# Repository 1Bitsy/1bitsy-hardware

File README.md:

# 1BitSy

This project includes 1BitSy evaluation boards. These boards are breadboard friendly STM32 (eventually other MCUs will be considered) with exposed Cortex JTAG and SWD interfaces. This allows the use of the Black Magic Probe, instead of the usually very limited built in debugger hardware.

Currently we have the following eval boards:

* 1BitSy V1.0d -> STM32F4x5RGT6

You can find the datasheet of the STM32F415RGT6 chip on the
[STMicroelectronics website](http://www.st.com/content/st_com/en/products/microcontrollers/stm32-32-bit-arm-cortex-mcus/stm32f4-series/stm32f405-415/stm32f415rg.html).

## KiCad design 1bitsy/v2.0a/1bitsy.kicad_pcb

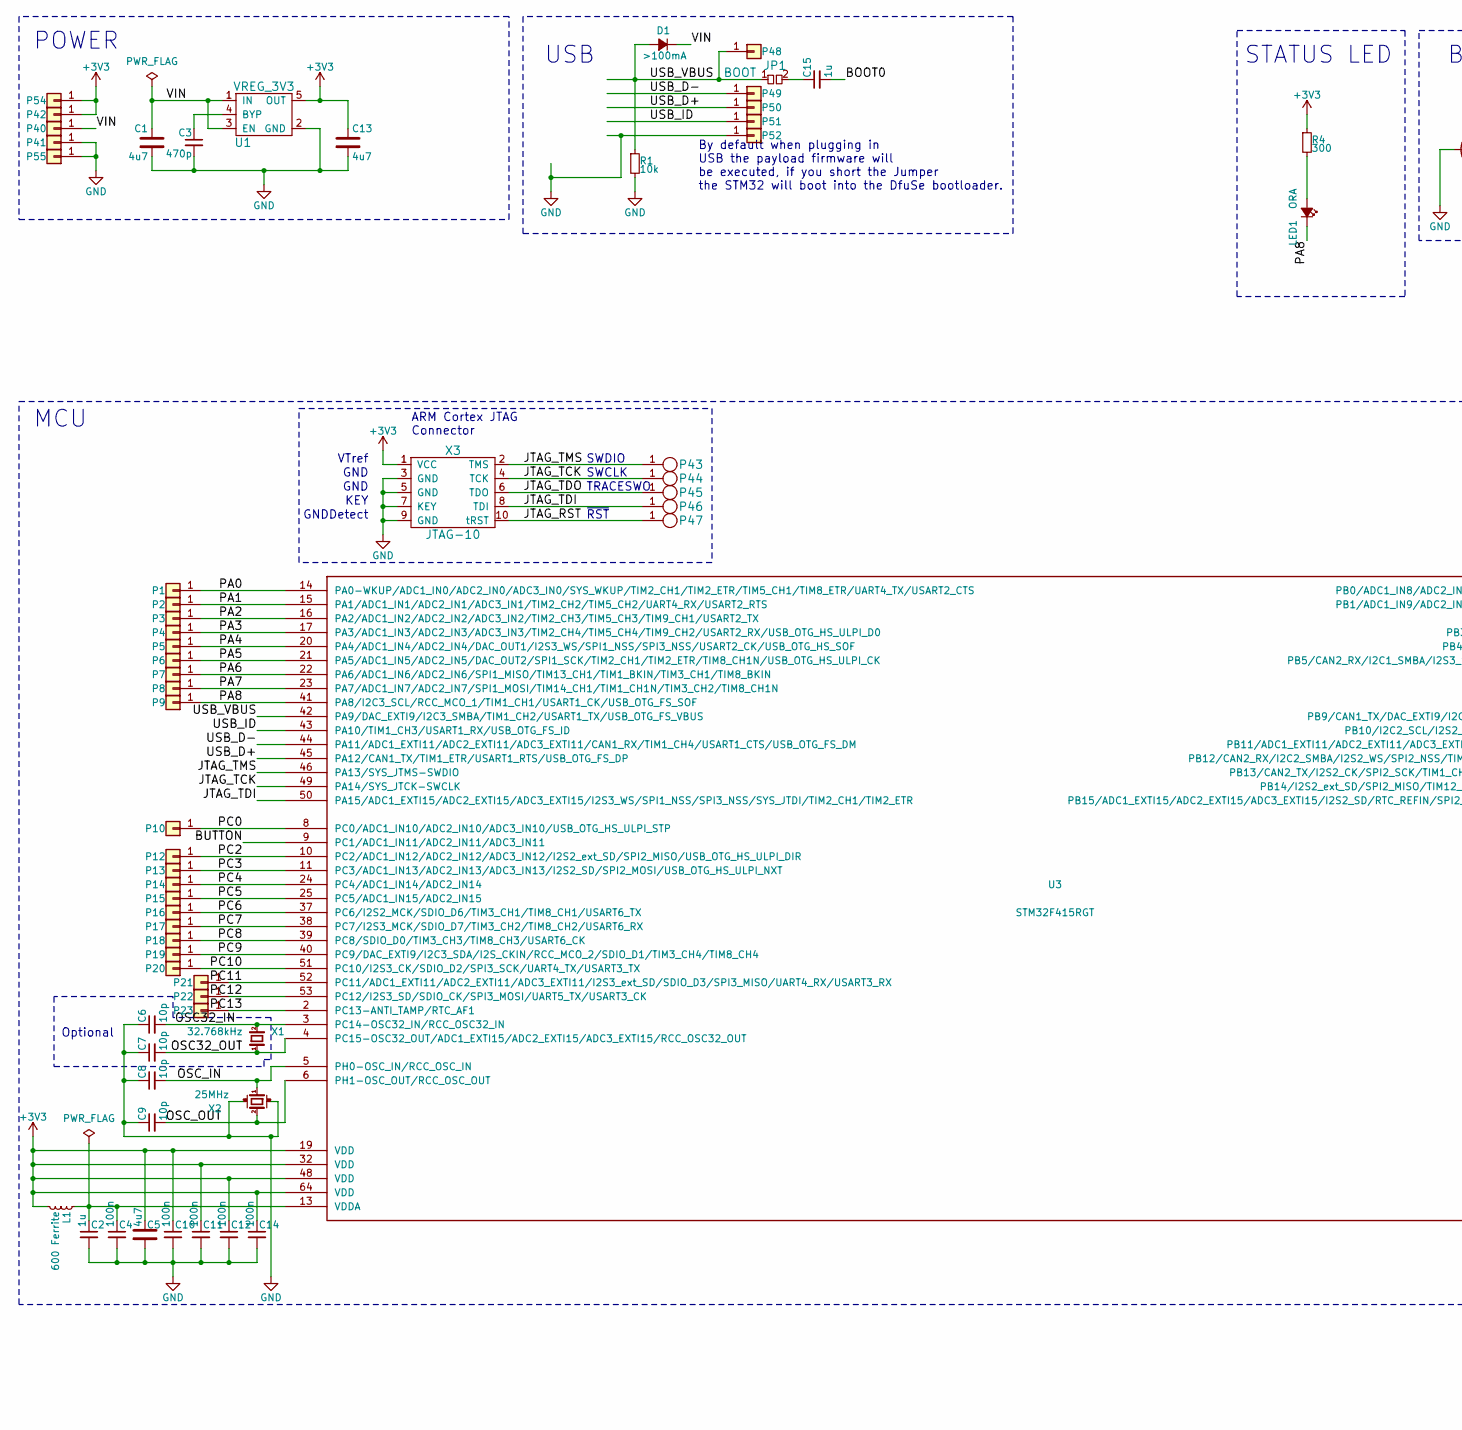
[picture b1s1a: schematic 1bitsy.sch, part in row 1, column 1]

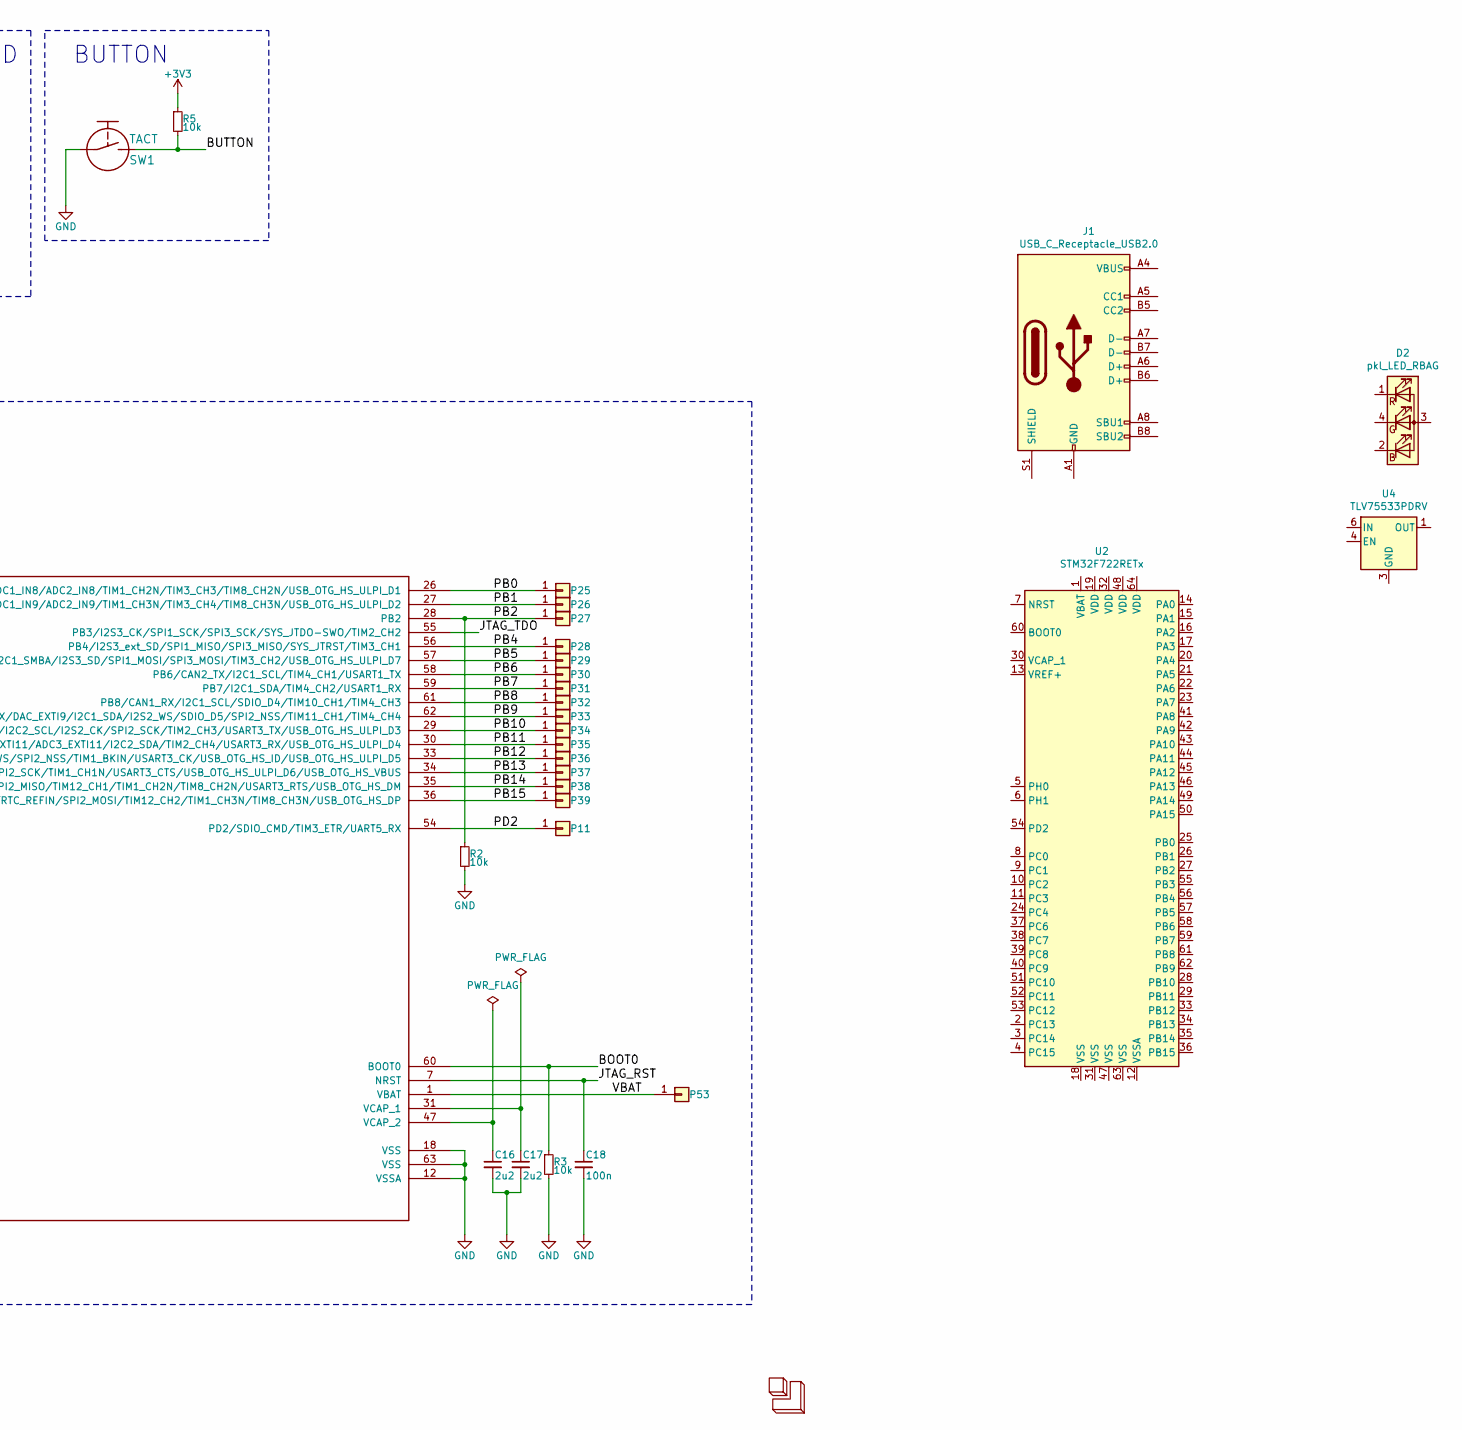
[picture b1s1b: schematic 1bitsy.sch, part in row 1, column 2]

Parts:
C1, C5, C13: 4u7; C_0603
C2, C15: 1u; C_0402
C3: 470p; C_0402
C4, C10, C11, C12, C14, C18: 100n; C_0402
C6, C7: 10p; C_0603
C8, C9: 10p; C_0402
C16, C17: 2u2; C_0402
D1: >100mA; D_0603
D2: pkl_LED_RBAG; LED_TRI_2020
J1: USB_C_Receptacle_USB2.0; USB_C_Receptacle_HRO_TYPE-C-31-M-12
JP1: BOOT; J_0603
L1: 600 Ferrite; L_0402
LED1: ORA; D_0603
LOGO1: 1BitSquared; 1b2_Logo_SilkS_7.5mm
P1, P2, P3, P4, P5, P6, P7, P8, P9, P10, P11, P12, P13, P14, P15, P16, P17, P18, P19, P20, P21, P22, P23, P25, P26, P27, P28, P29, P30, P31, P32, P33, P34, P35, P36, P37, P38, P39, P40, P41, P42, P53, P54, P55: CONN_01X01; Pin_Header_Straight_Round_1x01
P43, P44, P45, P46, P47: TP; POGO_PAD_SMD_R_1x1
P48, P49, P50, P51, P52: CONN_01X01; PAD_SMD_1x2.65
R1, R2, R3, R5: 10k; R_0402
R4: 300; R_0402
SW1: TACT; Tact_Switch_Top_B3U-1000P
U1: VREG_3V3; SOT-23-5
U2: STM32F722RETx; LQFP-64_10x10mm_P0.5mm
U3: STM32F415RGT; LQFP-64_10x10mm_Pitch0.5mm
U4: TLV75533PDRV; WSON-6-1EP_2x2mm_P0.65mm_EP1x1.6mm
X1: 32.768kHz; ABS07
X2: 25MHz; ABM8
X3: JTAG-10; FTSH-105-XX-X-DV

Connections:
+3V3: C5.1, C10.1, C11.1, C12.1, C13.1, C14.1, L1.1, P42.1, P54.1, R4.1, R5.1, U1.5 (OUT), U3.19 (VDD), U3.32 (VDD), U3.48 (VDD), U3.64 (VDD), X3.1 (VCC)
/BOOT0: C15.2, R3.1, U3.60 (BOOT0)
/BUTTON: R5.2, SW1.2, U3.9 (PC1/ADC1_IN11/ADC2_IN11/ADC3_IN11)
/JTAG_RST: C18.1, P47.1, U3.7 (NRST), X3.10 (tRST)
/JTAG_TCK: P44.1, U3.49 (PA14/SYS_JTCK-SWCLK), X3.4 (TCK)
/JTAG_TDI: P46.1, U3.50 (PA15/ADC1_EXTI15/ADC2_EXTI15/ADC3_EXTI1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), X3.8 (TDI)
/JTAG_TDO: P45.1, U3.55 (PB3/I2S3_CK/SPI1_SCK/SPI3_SCK/SYS_JTDO-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), X3.6 (TDO)
/JTAG_TMS: P43.1, U3.46 (PA13/SYS_JTMS-SWDIO), X3.2 (TMS)
/OSC32_IN: C6.2, U3.3 (PC14-OSC32_IN/RCC_OSC32_IN), X1.2
/OSC32_OUT: C7.2, U3.4 (PC15-OSC32_OUT/ADC1_EXTI15/ADC2_EXTI15/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), X1.1
/OSC_IN: C8.2, U3.5 (PH0-OSC_IN/RCC_OSC_IN), X2.1
/OSC_OUT: C9.2, U3.6 (PH1-OSC_OUT/RCC_OSC_OUT), X2.2
/PA0: P1.1, U3.14 (PA0-WKUP/ADC1_IN0/ADC2_IN0/ADC3_IN0/SYS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)
/PA1: P2.1, U3.15 (PA1/ADC1_IN1/ADC2_IN1/ADC3_IN1/TIM2_CH2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)
/PA2: P3.1, U3.16 (PA2/ADC1_IN2/ADC2_IN2/ADC3_IN2/TIM2_CH3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)
/PA3: P4.1, U3.17 (PA3/ADC1_IN3/ADC2_IN3/ADC3_IN3/TIM2_CH4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)
/PA4: P5.1, U3.20 (PA4/ADC1_IN4/ADC2_IN4/DAC_OUT1/I2S3_WS/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)
/PA5: P6.1, U3.21 (PA5/ADC1_IN5/ADC2_IN5/DAC_OUT2/SPI1_SCK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)
/PA6: P7.1, U3.22 (PA6/ADC1_IN6/ADC2_IN6/SPI1_MISO/TIM13_C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)
/PA7: P8.1, U3.23 (PA7/ADC1_IN7/ADC2_IN7/SPI1_MOSI/TIM14_C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)
/PA8: LED1.C, P9.1, U3.41 (PA8/I2C3_SCL/RCC_MCO_1/TIM1_CH1/USART1_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)
/PB0: P25.1, U3.26 (PB0/ADC1_IN8/ADC2_IN8/TIM1_CH2N/TIM3_CH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)
/PB1: P26.1, U3.27 (PB1/ADC1_IN9/ADC2_IN9/TIM1_CH3N/TIM3_CH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)
/PB2: P27.1, R2.1, U3.28 (PB2)
/PB4: P28.1, U3.56 (PB4/I2S3_ext_SD/SPI1_MISO/SPI3_MISO/SYS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)
/PB5: P29.1, U3.57 (PB5/CAN2_RX/I2C1_SMBA/I2S3_SD/SPI1_MOSI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)
/PB6: P30.1, U3.58 (PB6/CAN2_TX/I2C1_SCL/TIM4_CH1/USART1_TX)
/PB7: P31.1, U3.59 (PB7/I2C1_SDA/TIM4_CH2/USART1_RX)
/PB8: P32.1, U3.61 (PB8/CAN1_RX/I2C1_SCL/SDIO_D4/TIM10_CH1/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)
/PB9: P33.1, U3.62 (PB9/CAN1_TX/DAC_EXTI9/I2C1_SDA/I2S2_WS/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)
/PB10: P34.1, U3.29 (PB10/I2C2_SCL/I2S2_CK/SPI2_SCK/TIM2_CH3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)
/PB11: P35.1, U3.30 (PB11/ADC1_EXTI11/ADC2_EXTI11/ADC3_EXTI1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)
/PB12: P36.1, U3.33 (PB12/CAN2_RX/I2C2_SMBA/I2S2_WS/SPI2_NSS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)
/PB13: P37.1, U3.34 (PB13/CAN2_TX/I2S2_CK/SPI2_SCK/TIM1_CH1N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)
/PB14: P38.1, U3.35 (PB14/I2S2_ext_SD/SPI2_MISO/TIM12_CH1/TI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)
/PB15: P39.1, U3.36 (PB15/ADC1_EXTI15/ADC2_EXTI15/ADC3_EXTI1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)
/PC0: P10.1, U3.8 (PC0/ADC1_IN10/ADC2_IN10/ADC3_IN10/USB_O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)
/PC2: P12.1, U3.10 (PC2/ADC1_IN12/ADC2_IN12/ADC3_IN12/I2S2_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)
/PC3: P13.1, U3.11 (PC3/ADC1_IN13/ADC2_IN13/ADC3_IN13/I2S2_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)
/PC4: P14.1, U3.24 (PC4/ADC1_IN14/ADC2_IN14)
/PC5: P15.1, U3.25 (PC5/ADC1_IN15/ADC2_IN15)
/PC6: P16.1, U3.37 (PC6/I2S2_MCK/SDIO_D6/TIM3_CH1/TIM8_CH1/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)
/PC7: P17.1, U3.38 (PC7/I2S3_MCK/SDIO_D7/TIM3_CH2/TIM8_CH2/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)
/PC8: P18.1, U3.39 (PC8/SDIO_D0/TIM3_CH3/TIM8_CH3/USART6_CK)
/PC9: P19.1, U3.40 (PC9/DAC_EXTI9/I2C3_SDA/I2S_CKIN/RCC_MCO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)
/PC10: P20.1, U3.51 (PC10/I2S3_CK/SDIO_D2/SPI3_SCK/UART4_TX/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)
/PC11: P21.1, U3.52 (PC11/ADC1_EXTI11/ADC2_EXTI11/ADC3_EXTI1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)
/PC12: P22.1, U3.53 (PC12/I2S3_SD/SDIO_CK/SPI3_MOSI/UART5_TX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)
/PC13: P23.1, U3.2 (PC13-ANTI_TAMP/RTC_AF1)
/PD2: P11.1, U3.54 (PD2/SDIO_CMD/TIM3_ETR/UART5_RX)
/USB_D+: P50.1, U3.45 (PA12/CAN1_TX/TIM1_ETR/USART1_RTS/USB_OT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)
/USB_D-: P49.1, U3.44 (PA11/ADC1_EXTI11/ADC2_EXTI11/ADC3_EXTI1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)
/USB_ID: P51.1, U3.43 (PA10/TIM1_CH3/USART1_RX/USB_OTG_FS_ID)
/USB_VBUS: D1.A, JP1.1, P48.1, R1.1, U3.42 (PA9/DAC_EXTI9/I2C3_SMBA/TIM1_CH2/USART1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)
/VBAT: P53.1, U3.1 (VBAT)
/VIN: C1.1, D1.C, P40.1, U1.1 (IN), U1.3 (EN)
GND: C1.2, C2.2, C3.2, C4.2, C5.2, C6.1, C7.1, C8.1, C9.1, C10.2, C11.2, C12.2, C13.2, C14.2, C16.2, C17.2, C18.2, P41.1, P52.1, P55.1, R1.2, R2.2, R3.2, SW1.1, U1.2 (GND), U3.12 (VSSA), U3.18 (VSS), U3.63 (VSS), X2.GND (case), X3.3 (GND), X3.5 (GND), X3.7 (KEY), X3.9 (GND)
unnamed: C2.1, C4.1, L1.2, U3.13 (VDDA)
unnamed: C3.1, U1.4 (BYP)
unnamed: C15.1, JP1.2
unnamed: C16.1, U3.47 (VCAP_2)
unnamed: C17.1, U3.31 (VCAP_1)
unnamed: J1.A1 (GND), J1.A12 (GND), J1.B1 (GND), J1.B12 (GND)
unnamed: J1.A4 (VBUS), J1.A9 (VBUS), J1.B4 (VBUS), J1.B9 (VBUS)
unnamed: LED1.A, R4.2
unnamed: U4.3 (GND), U4.7 (GND)

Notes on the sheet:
SWDIO
SWCLK
TRACESWO
~RST
GND
KEY
GNDDetect
VTref
ARM Cortex JTAG Connector
USB
BUTTON
STATUS LED
MCU
Optional
By default when plugging in USB the payload firmware will be executed, if you short the Jumper the STM32 will boot into the DfuSe bootloader.
POWER

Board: 4 copper layers, 92 parts (14 on the bottom side), 66 nets, no tracks yet.

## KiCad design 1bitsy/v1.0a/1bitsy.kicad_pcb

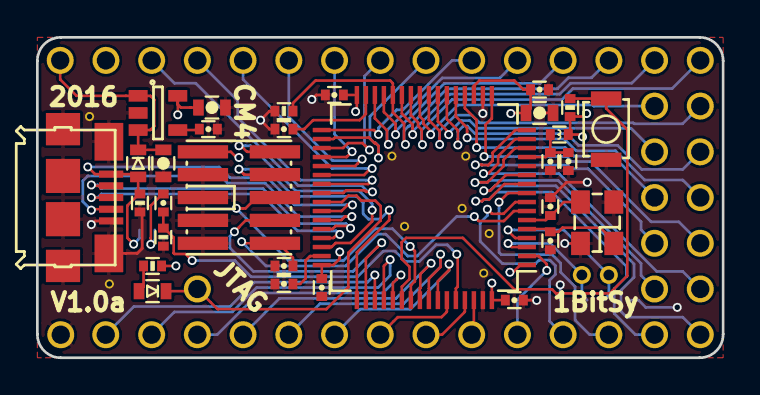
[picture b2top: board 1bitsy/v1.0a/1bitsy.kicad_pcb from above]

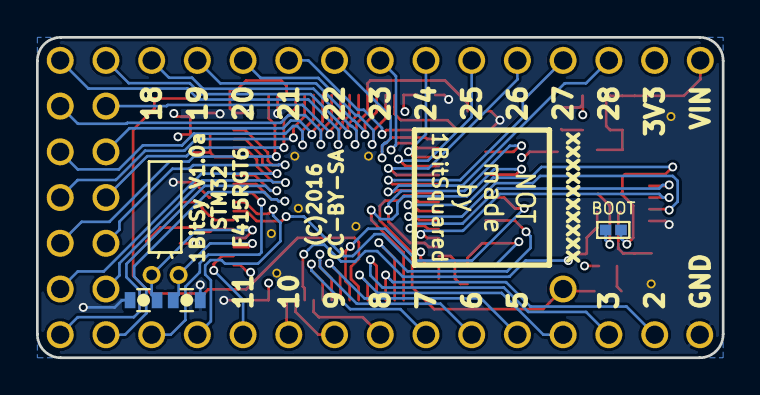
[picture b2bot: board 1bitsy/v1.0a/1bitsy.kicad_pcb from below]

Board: 4 copper layers, 38.1 x 17.8 mm, 76 parts (5 on the bottom side), 62 nets.

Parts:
C1, C5, C13: 4u7; C_0603
C2, C15: 1u; C_0402
C3: 470p; C_0402
C4, C10, C11, C12, C14, C18: 100n; C_0402
C6, C7: 10p; C_0603
C8, C9: 10p; C_0402
C16, C17: 2u2; C_0402
D1: >100mA; D_0603
J1: BOOT; J_0402
L1: 600 Ferrite; L_0402
LED1: ORA; D_0603
LOGO1: 1BitSquared; null_Logo_SilkS_7.5mm
P1, P2, P3, P4, P5, P6, P7, P8, P9, P10, P11, P12, P13, P14, P15, P16, P17, P18, P19, P20, P21, P22, P23, P25, P26, P27, P28, P29, P30, P31, P32, P33, P34, P35, P36, P37, P38, P39, P40, P41, P42: CONN_01X01; Pin_Header_Straight_Round_1x01
P24: USB_OTG; Connector_USB_Micro_B_SMD
R1, R2, R3, R5: 10k; R_0402
R4: 300; R_0402
SW1: TACT_G; Tact_Switch_Top_B3U-1000P
U1: VREG_3V3; SOT-23-5
U2: STM32F415RGT; LQFP-64_10x10mm_Pitch0.5mm
X1: 32.768kHz; Crystal_Round_Horizontal_2mm
X2: 25MHz; ABM8
X3: JTAG-10; FTSH-105-XX-X-DV

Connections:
+3V3: C5.1, C10.1, C11.1, C12.1, C13.1, C14.1, L1.1, P42.1, R4.1, R5.1, U1.5, U2.1, U2.19, U2.32, U2.48, U2.64, X3.1
/BOOT0: C15.2, R3.1, U2.60
/BUTTON: R5.2, SW1.2, U2.54
/JTAG_RST: C18.1, U2.7, X3.10
/JTAG_TCK: U2.49, X3.4
/JTAG_TDI: U2.50, X3.8
/JTAG_TDO: U2.55, X3.6
/JTAG_TMS: U2.46, X3.2
/OSC32_IN: C6.2, U2.3, X1.2
/OSC32_OUT: C7.2, U2.4, X1.1
/OSC_IN: C8.2, U2.5, X2.1
/OSC_OUT: C9.2, U2.6, X2.2
/PA0: P1.1, U2.14
/PA1: P2.1, U2.15
/PA2: P3.1, U2.16
/PA3: P4.1, U2.17
/PA4: P5.1, U2.20
/PA5: P6.1, U2.21
/PA6: P7.1, U2.22
/PA7: P8.1, U2.23
/PA8: LED1.C, P9.1, U2.41
/PB0: P25.1, U2.26
/PB1: P26.1, U2.27
/PB2: P27.1, R2.1, U2.28
/PB4: P28.1, U2.56
/PB5: P29.1, U2.57
/PB6: P30.1, U2.58
/PB7: P31.1, U2.59
/PB8: P32.1, U2.61
/PB9: P33.1, U2.62
/PB10: P34.1, U2.29
/PB11: P35.1, U2.30
/PB12: P36.1, U2.33
/PB13: P37.1, U2.34
/PB14: P38.1, U2.35
/PB15: P39.1, U2.36
/PC0: P10.1, U2.8
/PC1: P11.1, U2.9
/PC2: P12.1, U2.10
/PC3: P13.1, U2.11
/PC4: P14.1, U2.24
/PC5: P15.1, U2.25
/PC6: P16.1, U2.37
/PC7: P17.1, U2.38
/PC8: P18.1, U2.39
/PC9: P19.1, U2.40
/PC10: P20.1, U2.51
/PC11: P21.1, U2.52
/PC12: P22.1, U2.53
/PC13: P23.1, U2.2
/USB_D+: P24.3, U2.45
/USB_D-: P24.2, U2.44
/USB_ID: P24.4, U2.43
/USB_VBUS: D1.A, J1.1, P24.1, R1.1, U2.42
/VIN: C1.1, D1.C, P40.1, U1.1, U1.3
GND: C1.2, C2.2, C3.2, C4.2, C5.2, C6.1, C7.1, C8.1, C9.1, C10.2, C11.2, C12.2, C13.2, C14.2, C16.2, C17.2, C18.2, P24.5, P24.GND, P41.1, R1.2, R2.2, R3.2, SW1.1, U1.2, U2.12, U2.18, U2.63, X2.GND, X3.3, X3.5, X3.7, X3.9
unnamed: C2.1, C4.1, L1.2, U2.13
unnamed: C3.1, U1.4
unnamed: C15.1, J1.2
unnamed: C16.1, U2.47
unnamed: C17.1, U2.31
unnamed: LED1.A, R4.2

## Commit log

2016-05-21 Initial commit of the repo skeleton.
2016-05-25 Initial commit of 1BitSy V1.0a
2016-05-25 Initial commit of README.
2016-06-02 Added V1.0 pinout legend.
2016-06-02 Added legend graphic to the README.
2016-06-02 Add Gitter badge (#1)
2016-07-17 Initial commit of V1.0b.
    * Added wire pads for USB
    * Added pogopin pads for JTAG
2016-07-22 Updated PKL.
2016-07-22 First routing pass on 1BitSy V1.0b.
2016-07-22 Some more layout and legend cleanup.
2016-07-22 Swapped PA6/PA7 pads to follow pattern. Added pin legend.
2016-07-23 Some more silkscreen legend cleanup.
2016-07-23 Final prototype production sync.
2016-07-23 Forgot to move a GND via.
2016-07-23 Fixed a 3v3 via.
    It was not a problem for gerber generation, but the dev kicad branch
    disconnected it on import.
2016-07-23 Made the legend split line split.
2016-07-29 Update gitter badge.
2016-08-15 Improved part ID and Value legend.
2016-08-16 Added legend diagram for 1BitSy V1.0b.
2016-08-20 Added legend of the "second layer" pins.
2016-08-20 Added back side legend.
2016-08-20 Added missing DAC/ADC labels.
2016-08-20 Added back side legend to the README.
2016-08-20 Initial commit of V1.0c.
    Only copy and version bump.
2016-08-21 Exposed the PD2 pin to allow 4pin SDIO.
    The PD2 pin was connected to the button making 4bit SDIO difficult to
    implement. This resulted in a bunch of IO pins changing their positions:
    * Button: PD2 -> PC1
    * 5: PB4 -> PD2
    * 6: PB5 -> PB4
    * 7: PB6 -> PB5
2016-08-22 Changed the boot jumper to 0603 size.
    This should make manual soldering of it slightly easier.
2016-08-22 Updated footprints.
    The new dipol footprints do not have the 0.075mm solderstop opening
    constraint.
2016-08-25 Added 1Bitsy logo. Improved back side silkscreen.
2016-08-26 A lot of silkscreen work.
2016-08-26 More silkscreen polish.
    Made the pixelheart larger, moved some via away from silkscreen lines.
2016-08-26 Removed serial pin numbering, left only pin bank+pin no.
    We got rid of the pcb specific numbering to make space for larger
    internal mcu numbering labels. These are much more important when
    writing code for the board.
2016-08-27 Some more Silkscreen cleanup work.
2016-08-27 Swapped C4 & C5 for consistency.
2016-08-27 Updated Fab legend.
2016-08-27 Recovered v1.0c pcb revision, added v1.0d.
2016-08-27 Updated legends for and to V1.0d.
2016-09-10 Added a rounded rectangle pad 1bitsy v1.0d.
    The rounded rectangles are recommended by IPC. the advantages are:
    * Better flow of pb free solder
    * Better detach of solder paste from stencils
    * Better part joint fillet
2016-09-10 Updated 1bitsy hardware lib.
2016-09-10 updated 1bitsy-hardware-lib
2016-09-10 Fixed the LS crystal label.
    We had 36KHz but should be 32KHz if anything. (yes we are truncating the
    actual frequency because we lack space for all the stuff behind the
    comma)
2016-09-10 Added 1bitsy hardware library.
2016-09-21 Some minor adjustment for pos file generation.
2016-10-11 Added link to the STM32F415RGT6 in the README.
2016-10-29 Added 1Bitsy pinout legend PDF.
2016-11-14 Added schematic in pdf format.
2017-04-09 Added postcard files to the repository.
2020-07-31 WIP migration + v2.0a
2020-08-05 More WIP

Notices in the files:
1bitsy/v1.0a/1bitsy.kicad_pcb:
(C) 2016 Piotr Esden-Tempski
(C) 2016 1BitSquared LLC
License: CC-BY-SA V4.0
CC-BY-SA
1bitsy/v2.0a/1bitsy.kicad_pcb:
© 2016-2020 1BitSquared
© 2016 Piotr Esden-Tempski
© 2020 Jordi Pakey-Rodriguez
License: CC BY-SA 4.0
(C)2016 CC-BY-SA
